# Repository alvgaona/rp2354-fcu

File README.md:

<div align="center">

# rp2354-fcu

**A 40 × 40 mm flight control unit built around the RP2354A.**

</div>

## Overview

rp2354-fcu is a 2-layer flight controller that fits the 30.5 mm mounting pattern. It takes a 2S LiPo or USB, reads an IMU and a GPS, and drives eight servos or ESCs.

- RP2354A microcontroller with 2 MB of flash in the package
- ICM-42688-P IMU on SPI
- GPS connector (JST-GH) for an off-board module such as the NEO-6M
- Eight 3-pin servo/ESC outputs
- 2S LiPo (JST-XH) or USB-C power through a 3.3 V buck converter
- SWD on JST-SH in the Raspberry Pi debug probe pinout

The MCU core (regulator, crystal, decoupling and USB) is copied from Raspberry Pi's RP2350A minimal design, including its layout.

Rev 0.1.0 passes KiCad's ERC and DRC, but it has not been manufactured or tested yet.

The [hardware reference](docs/hardware.md) has the power notes, the GPIO map, the connector pinouts and how to order the board from JLCPCB.

## Build

The design lives in `hw/` and is the source of truth, so edit it in KiCad 10. The build checks it and writes everything you need to order and view the board.

You need KiCad 10 and [pixi](https://pixi.sh). Install the font `hw/fonts/IBMPlexMono-Medium.ttf` first (double-click it), because the text on the back of the board uses it.

```sh
pixi run build
```

The build runs ERC, DRC with schematic parity, and `scripts/check_layout.py`, and stops on any error before it exports anything. That last script checks what DRC cannot. It wants a ground via near every ground pad, the ground pour in one solid piece, no pad fed only by a thin 3.3 V track, and nothing drilled under the IMU.

It then writes these files to `build/`.

- Gerbers, BOM and placement files for JLCPCB (`fc-gerbers.zip`, `fc-bom.csv` and `fc-cpl.csv`)
- The schematic as a PDF (`fc-schematic.pdf`)
- The assembled board in 3D (`fc.glb`)
- The board package with all of the above plus the KiCad files (`fc-rev<rev>.zip`)

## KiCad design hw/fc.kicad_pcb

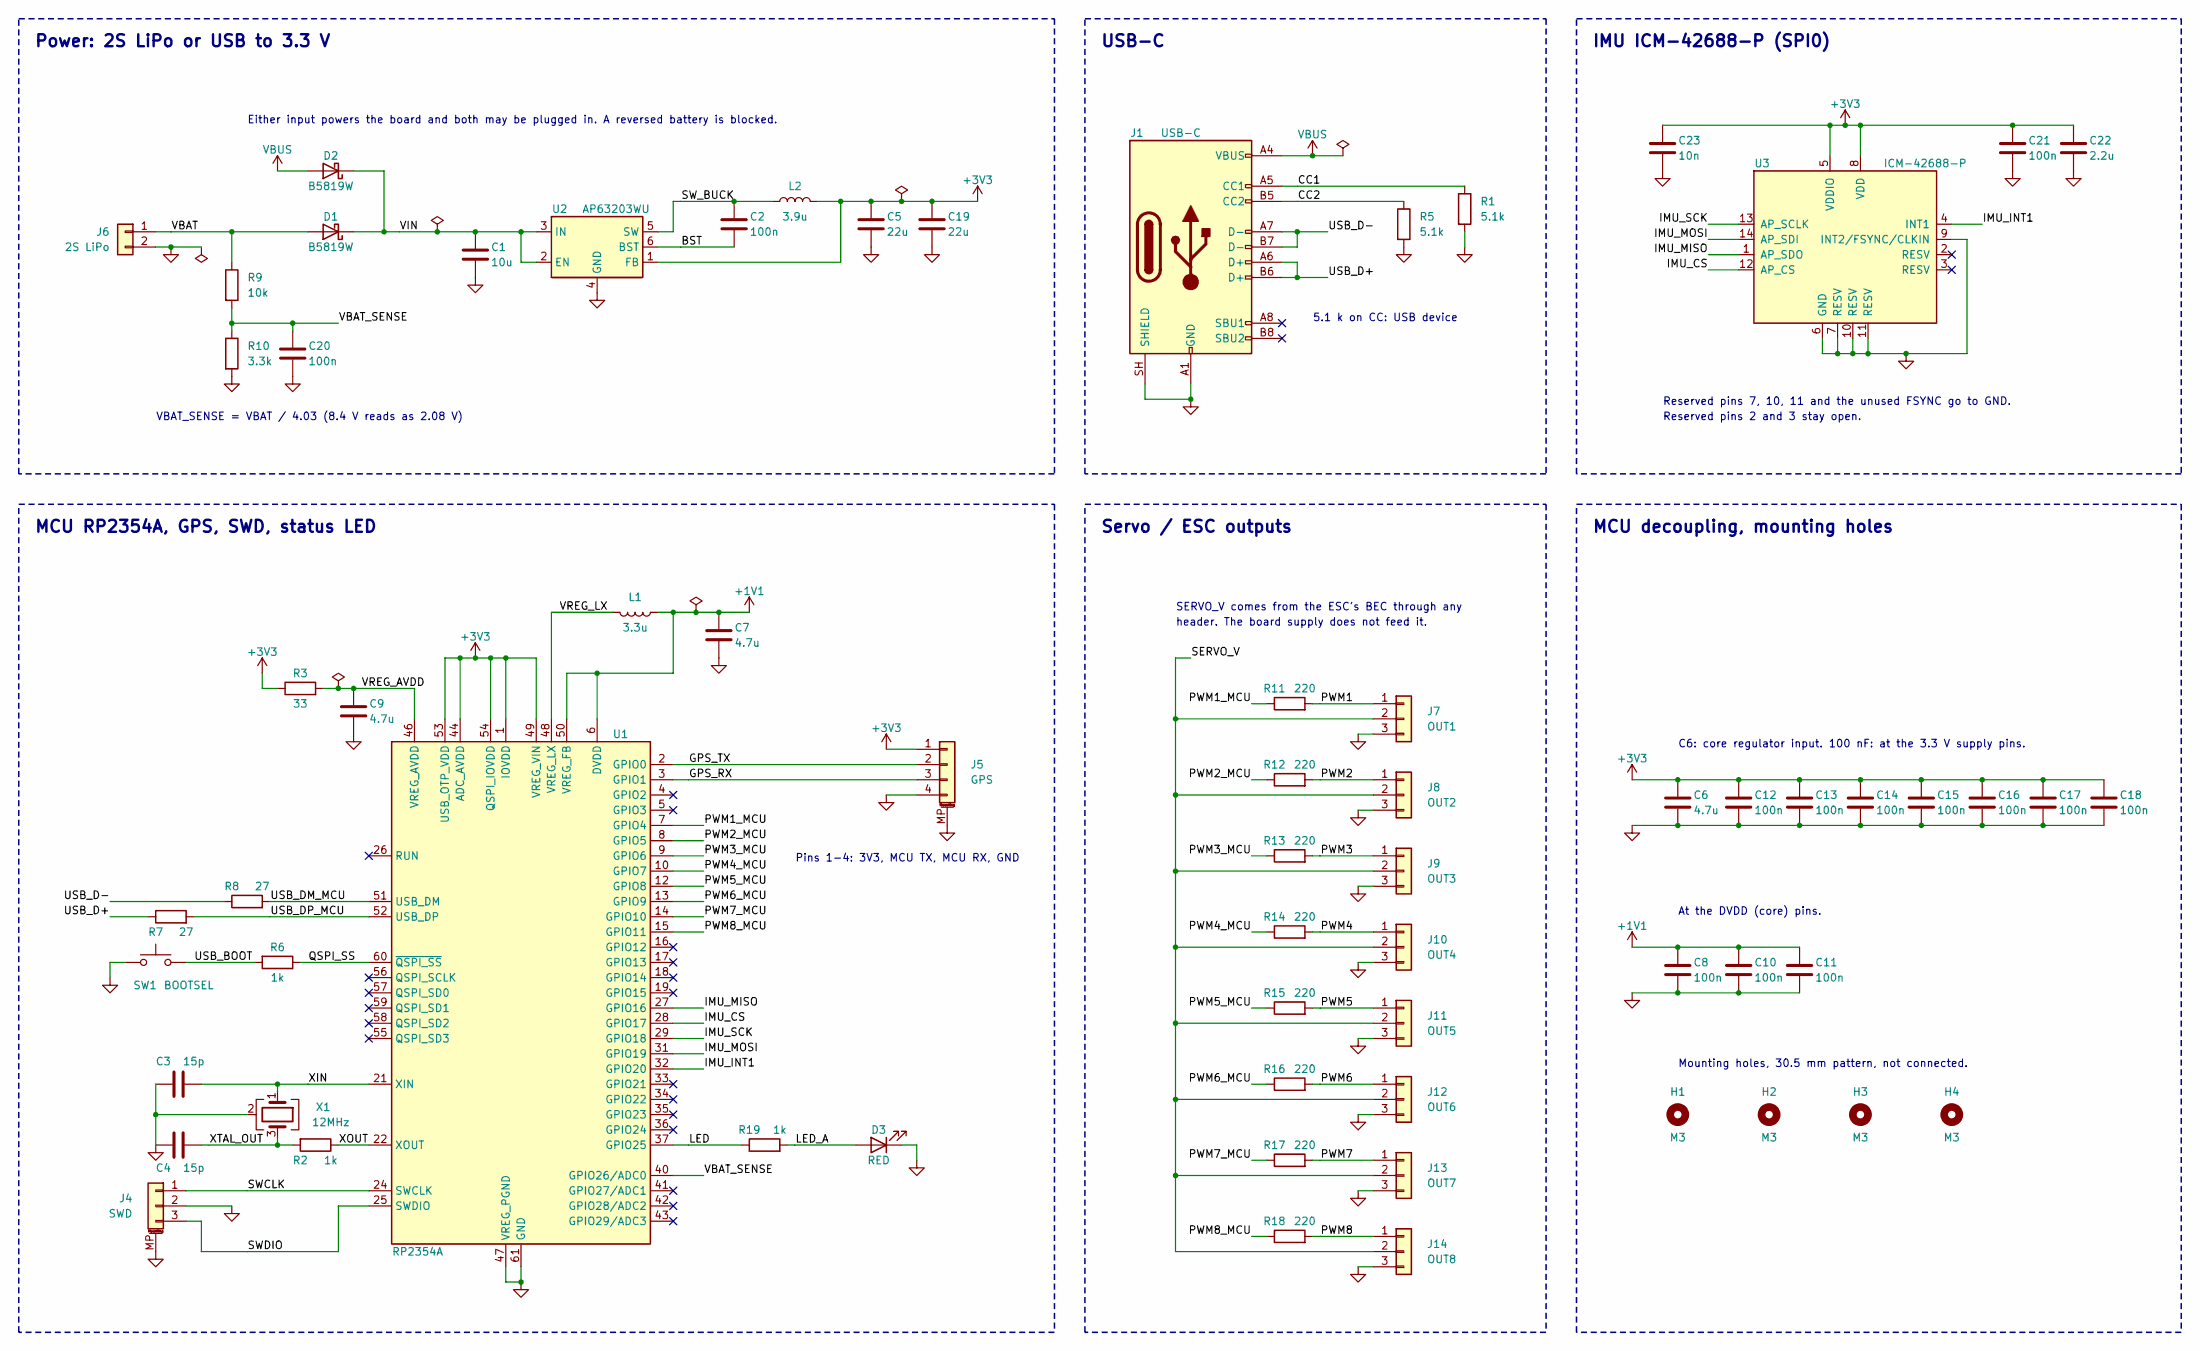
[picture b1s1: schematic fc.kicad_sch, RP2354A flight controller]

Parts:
C1: 10u; C_0805_2012Metric; MPN CL21A106KAYNNNE; LCSC C15850
C2, C20, C21: 100n; C_0402_1005Metric; MPN CL05B104KO5NNNC; LCSC C1525
C3, C4: 15p; generic_capc1005x50; MPN GRM1555C1H150JA01D; LCSC C76950
C5, C19: 22u; C_0805_2012Metric; MPN CL21A226MAQNNNE; LCSC C45783
C6, C7: 4.7u; generic_capc1005x50_wide; MPN GRM155R60J475ME47D; LCSC C82453
C8, C10, C11, C12, C13, C14, C15, C16, C17, C18: 100n; generic_capc1005x50; MPN CL05B104KO5NNNC; LCSC C1525
C9: 4.7u; generic_capc1005x50; MPN GRM155R60J475ME47D; LCSC C82453
C22: 2.2u; C_0402_1005Metric; MPN CL05A225MQ5NSNC; LCSC C12530
C23: 10n; C_0402_1005Metric; MPN CL05B103KB5NNNC; LCSC C15195
D1, D2: B5819W; D_SOD-123; MPN B5819W SL; LCSC C8598
D3: RED; LED_0603_1608Metric; MPN KT-0603R; LCSC C2286
H1, H2, H3, H4: M3; MountingHole_3.2mm_M3
J1: USB-C; USB_C_Receptacle_HRO_TYPE-C-31-M-12; MPN TYPE-C-31-M-12; LCSC C165948
J4: SWD; JST_SH_SM03B-SRSS-TB_1x03-1MP_P1.00mm_Horizontal; MPN SM03B-SRSS-TB(LF)(SN); LCSC C160403
J5: GPS; JST_GH_SM04B-GHS-TB_1x04-1MP_P1.25mm_Horizontal; MPN SM04B-GHS-TB(LF)(SN); LCSC C189895
J6: 2S LiPo; JST_XH_B2B-XH-A_1x02_P2.50mm_Vertical; MPN B2B-XH-A(LF)(SN); LCSC C158012
J7: OUT1; PinHeader_1x03_P2.54mm_Vertical_Tight; MPN 2.54-1*3P; LCSC C49257
J8: OUT2; PinHeader_1x03_P2.54mm_Vertical_Tight; MPN 2.54-1*3P; LCSC C49257
J9: OUT3; PinHeader_1x03_P2.54mm_Vertical_Tight; MPN 2.54-1*3P; LCSC C49257
J10: OUT4; PinHeader_1x03_P2.54mm_Vertical_Tight; MPN 2.54-1*3P; LCSC C49257
J11: OUT5; PinHeader_1x03_P2.54mm_Vertical_Tight; MPN 2.54-1*3P; LCSC C49257
J12: OUT6; PinHeader_1x03_P2.54mm_Vertical_Tight; MPN 2.54-1*3P; LCSC C49257
J13: OUT7; PinHeader_1x03_P2.54mm_Vertical_Tight; MPN 2.54-1*3P; LCSC C49257
J14: OUT8; PinHeader_1x03_P2.54mm_Vertical_Tight; MPN 2.54-1*3P; LCSC C49257
L1: 3.3u; abracon_aota-b201610s3r3-101-t; MPN AOTA-B201610S3R3-101-T; LCSC C42411119
L2: 3.9u; L_Changjiang_FNR3015S; MPN FNR3015S3R9MT; LCSC C167751
R1, R5: 5.1k; R_0402_1005Metric; MPN 0402WGF5101TCE; LCSC C25905
R2: 1k; generic_resc1005x35; MPN 0402WGF1001TCE; LCSC C11702
R3: 33; generic_resc1005x35; MPN 0402WGF330JTCE; LCSC C25105
R6, R19: 1k; R_0402_1005Metric; MPN 0402WGF1001TCE; LCSC C11702
R7, R8: 27; generic_resc1005x35; MPN 0402WGF270JTCE; LCSC C25100
R9: 10k; R_0402_1005Metric; MPN 0402WGF1002TCE; LCSC C25744
R10: 3.3k; R_0402_1005Metric; MPN 0402WGF3301TCE; LCSC C25890
R11, R12, R13, R14, R15, R16, R17, R18: 220; R_0402_1005Metric; MPN 0402WGF2200TCE; LCSC C25091
SW1: BOOTSEL; wurthelek_434133025816; MPN 434133025816; LCSC C5504987
U1: RP2354A; rpi_rp2350a_vias; MPN RP2354A; LCSC C41378174
U2: AP63203WU; TSOT-23-6; MPN AP63203WU-7; LCSC C780769
U3: ICM-42688-P; LGA-14_L3.0-W2.5-P0.50-TL; MPN ICM-42688-P; LCSC C1850418
X1: 12MHz; generic_xtalcc320x250x80-4; MPN ABM8-272-T3; LCSC C20625731

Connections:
+1V1: C7.1, C8.1, C10.1, C11.1, L1.1, U1.6 (DVDD), U1.23 (DVDD), U1.39 (DVDD), U1.50 (VREG_FB)
+3V3: C5.1, C6.1, C12.1, C13.1, C14.1, C15.1, C16.1, C17.1, C18.1, C19.1, C21.1, C22.1, C23.1, J5.1, L2.2, R3.1, U1.1 (IOVDD), U1.11 (IOVDD), U1.20 (IOVDD), U1.30 (IOVDD), U1.38 (IOVDD), U1.44 (ADC_AVDD), U1.45 (IOVDD), U1.49 (VREG_VIN), U1.53 (USB_OTP_VDD), U1.54 (QSPI_IOVDD), U2.1 (FB), U3.5 (VDDIO), U3.8 (VDD)
/BST: C2.1, U2.6 (BST)
/CC1: J1.A5 (CC1), R1.1
/CC2: J1.B5 (CC2), R5.1
/GPS_RX: J5.3, U1.3 (GPIO1)
/GPS_TX: J5.2, U1.2 (GPIO0)
/IMU_CS: U1.28 (GPIO17), U3.12 (AP_CS)
/IMU_INT1: U1.32 (GPIO20), U3.4 (INT1)
/IMU_MISO: U1.27 (GPIO16), U3.1 (AP_SDO)
/IMU_MOSI: U1.31 (GPIO19), U3.14 (AP_SDI)
/IMU_SCK: U1.29 (GPIO18), U3.13 (AP_SCLK)
/LED: R19.1, U1.37 (GPIO25)
/LED_A: D3.2 (A), R19.2
/PWM1: J7.1, R11.2
/PWM1_MCU: R11.1, U1.7 (GPIO4)
/PWM2: J8.1, R12.2
/PWM2_MCU: R12.1, U1.8 (GPIO5)
/PWM3: J9.1, R13.2
/PWM3_MCU: R13.1, U1.9 (GPIO6)
/PWM4: J10.1, R14.2
/PWM4_MCU: R14.1, U1.10 (GPIO7)
/PWM5: J11.1, R15.2
/PWM5_MCU: R15.1, U1.12 (GPIO8)
/PWM6: J12.1, R16.2
/PWM6_MCU: R16.1, U1.13 (GPIO9)
/PWM7: J13.1, R17.2
/PWM7_MCU: R17.1, U1.14 (GPIO10)
/PWM8: J14.1, R18.2
/PWM8_MCU: R18.1, U1.15 (GPIO11)
/QSPI_SS: R6.1, U1.60 (~QSPI_SS)
/SERVO_V: J7.2, J8.2, J9.2, J10.2, J11.2, J12.2, J13.2, J14.2
/SWCLK: J4.1, U1.24 (SWCLK)
/SWDIO: J4.3, U1.25 (SWDIO)
/SW_BUCK: C2.2, L2.1, U2.5 (SW)
/USB_BOOT: R6.2, SW1.3 (B), SW1.4 (B)
/USB_D+: J1.A6 (D+), J1.B6 (D+), R7.1
/USB_D-: J1.A7 (D-), J1.B7 (D-), R8.1
/USB_DM_MCU: R8.2, U1.51 (USB_DM)
/USB_DP_MCU: R7.2, U1.52 (USB_DP)
/VBAT: D1.2 (A), J6.1, R9.1
/VBAT_SENSE: C20.1, R9.2, R10.1, U1.40 (GPIO26/ADC0)
/VIN: C1.1, D1.1 (K), D2.1 (K), U2.2 (EN), U2.3 (IN)
/VREG_AVDD: C9.1, R3.2, U1.46 (VREG_AVDD)
/VREG_LX: L1.2, U1.48 (VREG_LX)
/XIN: C3.1, U1.21 (XIN), X1.1
/XOUT: R2.1, U1.22 (XOUT)
/XTAL_OUT: C4.1, R2.2, X1.3
GND: C1.2, C3.2, C4.2, C5.2, C6.2, C7.2, C8.2, C9.2, C10.2, C11.2, C12.2, C13.2, C14.2, C15.2, C16.2, C17.2, C18.2, C19.2, C20.2, C21.2, C22.2, C23.2, D3.1 (K), J1.A1 (GND), J1.A12 (GND), J1.B1 (GND), J1.B12 (GND), J1.SH (SHIELD), J4.2, J4.MP (MountPin), J5.4, J5.MP (MountPin), J6.2, J7.3, J8.3, J9.3, J10.3, J11.3, J12.3, J13.3, J14.3, R1.2, R5.2, R10.2, SW1.1 (A), SW1.2 (A), U1.47 (VREG_PGND), U1.61 (GND), U2.4 (GND), U3.6 (GND), U3.7 (RESV), U3.9 (INT2/FSYNC/CLKIN), U3.10 (RESV), U3.11 (RESV), X1.2 (G), X1.4 (G)
VBUS: D2.2 (A), J1.A4 (VBUS), J1.A9 (VBUS), J1.B4 (VBUS), J1.B9 (VBUS)

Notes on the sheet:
Either input powers the board and both may be plugged in. A reversed battery is blocked.
VBAT_SENSE = VBAT / 4.03 (8.4 V reads as 2.08 V)
Pins 1-4: 3V3, MCU TX, MCU RX, GND
5.1 k on CC: USB device
SERVO_V comes from the ESC's BEC through any
header. The board supply does not feed it.
Reserved pins 7, 10, 11 and the unused FSYNC go to GND.
Reserved pins 2 and 3 stay open.
C6: core regulator input. 100 nF: at the 3.3 V supply pins.
At the DVDD (core) pins.
Mounting holes, 30.5 mm pattern, not connected.
Power: 2S LiPo or USB to 3.3 V
MCU RP2354A, GPS, SWD, status LED
USB-C
Servo / ESC outputs
IMU ICM-42688-P (SPI0)
MCU decoupling, mounting holes

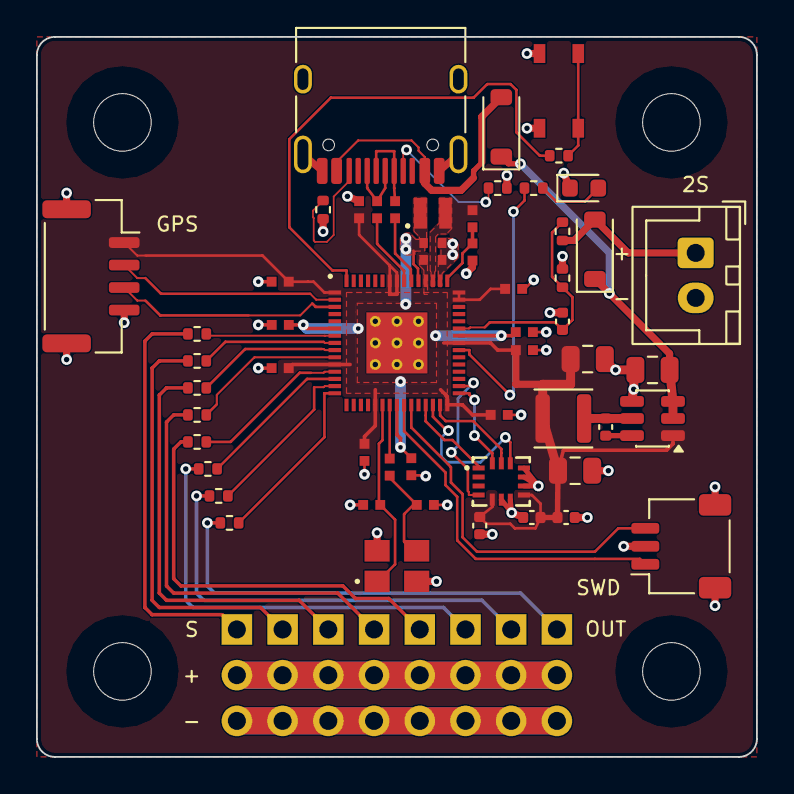
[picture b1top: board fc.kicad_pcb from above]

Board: 2 copper layers, 40.0 x 40.0 mm, 67 parts (0 on the bottom side), 50 nets.

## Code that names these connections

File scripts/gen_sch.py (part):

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    s.w(r9["2"], r10["1"])
    s.w((27.94, 45.72), (38.1, 45.72), c20["1"])
    s.w((38.1, 45.72), (45.72, 45.72))
    s.label("VBAT_SENSE", (45.72, 45.72))
    s.power("GND", r10["2"])
    s.power("GND", c20["2"])
    s.text("VBAT_SENSE = VBAT / 4.03 (8.4 V reads as 2.08 V)", 15.24, 62.23)
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    l2 = s.place("L2", 121.92, 25.4, a=90)
    c2 = s.place("C2", 111.76, 29.21, a=180)
    s.w(u2["5"], (101.6, 30.48), (101.6, 25.4), l2["1"])
    s.label("SW_BUCK", (102.87, 25.4))
    s.w(u2["6"], c2["1"])
    s.label("BST", (102.87, 33.02))
    s.w(l2["2"], (152.4, 25.4))
    s.w(u2["1"], (129.54, 35.56), (129.54, 25.4))
    for ref, x in (("C5", 134.62), ("C19", 144.78)):
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
def imu_block(s):
    u3 = s.place("U3", 60.96, 45.72, val_at=(67.31, 31.75, "left"))
    for pin, name, a in (("13", "IMU_SCK", 180), ("14", "IMU_MOSI", 180), ("1", "IMU_MISO", 180), ("12", "IMU_CS", 180),
                         ("4", "IMU_INT1", 0)):
        end = (u3[pin][0] + (5.08 if a == 0 else -5.08), u3[pin][1])
        s.w(u3[pin], end)
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    r3 = s.place("R3", 64.77, 50.8, a=90)
    c9 = s.place("C9", 73.66, 54.61)
    s.w(u1["46"], (83.82, 50.8), r3["2"])
    s.label("VREG_AVDD", (74.93, 50.8))
    s.power("FLAG", (71.12, 50.8))
    s.w(r3["1"], (58.42, 50.8), (58.42, 48.26))
    s.power("+3V3", (58.42, 48.26))
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    l1 = s.place("L1", 120.65, 38.1, a=270)
    c7 = s.place("C7", 134.62, 41.91)
    s.w(u1["48"], (106.68, 38.1), l1["2"])
    s.label("VREG_LX", (107.95, 38.1))
    s.w(l1["1"], (139.7, 38.1))
    s.w((127, 38.1), (127, 48.26), (109.22, 48.26), u1["50"])
    s.w(u1["6"], (114.3, 48.26))
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    r6 = s.place("R6", 60.96, 96.52, a=270)
    sw = s.place("SW1", 40.64, 96.52, ref_at=(36.83, 100.33, "left"), val_at=(41.91, 100.33, "left"))
    s.w(u1["60"], r6["1"])
    s.label("QSPI_SS", (66.04, 96.52))
    s.w(r6["2"], sw["3"])
    s.label("USB_BOOT", (46.99, 96.52))
    s.w(sw["1"], (33.02, 96.52), (33.02, 99.06))
    s.power("GND", (33.02, 99.06))

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    r2_ = s.place("R2", 67.31, 127, a=270, ref_at=(64.77, 129.54, None), val_at=(69.85, 129.54, None))
    s.w(u1["21"], c3["1"])
    s.w((60.96, 116.84), x1["1"])
    s.label("XIN", (66.04, 116.84))
    s.w(u1["22"], r2_["1"])
    s.label("XOUT", (71.12, 127))
    s.w(r2_["2"], c4["1"])
    s.w((60.96, 127), x1["3"])
    s.label("XTAL_OUT", (49.53, 127))
    s.w(c3["2"], c4["2"])
    s.w(x1["2"], (40.64, 121.92))
    s.power("GND", c4["2"])
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    # right: GPS connector straight across from UART0, signals that leave the block, status LED
    j5 = s.place("J5", 172.72, 63.5, ref_at=(176.53, 63.5, "left"), val_at=(176.53, 66.04, "left"))
    s.w(u1["2"], j5["2"])
    s.label("GPS_TX", (129.54, 63.5))
    s.w(u1["3"], j5["3"])
    s.label("GPS_RX", (129.54, 66.04))
    s.w(j5["1"], (162.56, 60.96))
    s.power("+3V3", (162.56, 60.96))
    s.w(j5["4"], (162.56, 68.58))
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    s.w(u1["37"], r19["1"])
    s.label("LED", (129.54, 127))
    s.w(r19["2"], d3["2"])
    s.label("LED_A", (147.32, 127))
    s.w(d3["1"], (167.64, 127), (167.64, 129.54))
    s.power("GND", (167.64, 129.54))

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        s.power("GND", (35.56, j["3"][1]))
        last = j["2"][1]
    s.w((7.62, 12.7), (5.08, 12.7), (5.08, last))
    s.label("SERVO_V", (7.62, 12.7))
    s.text("SERVO_V comes from the ESC's BEC through any", 5.08, 5.08)
    s.text("header. The board supply does not feed it.", 5.08, 7.62)

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
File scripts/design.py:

"""Single source of truth for the rev 0.1.0 flight-controller board.

Every part: ref -> (symbol, value, footprint, MPN, manufacturer, LCSC, {pin: net}).
Pins not listed get a no-connect flag. Refs of the RP2354A support circuit match
Raspberry Pi's RP2350A minimal design so build_pcb.py can transplant its layout.
"""

REV = "0.1.0"
TITLE = "RP2354A flight controller"

R0402 = "Resistor_SMD:R_0402_1005Metric"
C0402 = "Capacitor_SMD:C_0402_1005Metric"
C0805 = "Capacitor_SMD:C_0805_2012Metric"
# Footprints copied from the Raspberry Pi minimal design (layout transplanted as-is).
RC = "rpi:generic_capc1005x50"
RCW = "rpi:generic_capc1005x50_wide"
RR = "rpi:generic_resc1005x35"

PARTS = {}


def part(ref, sym, value, fp, mpn, mfr, lcsc, pins):
    PARTS[ref] = dict(sym=sym, value=value, fp=fp, mpn=mpn, mfr=mfr, lcsc=lcsc, pins=pins)


def R(ref, value, a, b, mpn, lcsc, fp=R0402):
    part(ref, "Device:R", value, fp, mpn, "UNI-ROYAL", lcsc, {"1": a, "2": b})


def C(ref, value, a, b, mpn, mfr, lcsc, fp=C0402):
    part(ref, "Device:C", value, fp, mpn, mfr, lcsc, {"1": a, "2": b})


# ---------------- MCU: RP2354A (2 MB flash in package) ----------------
GPIO = {
    2: "GPS_TX", 3: "GPS_RX",  # GPIO0/1 = UART0
    # GPIO4-11 = PWM slices 2-5. GPIO2/3 (pins 4/5) are left free: C8's vias block their escape.
    7: "PWM1_MCU", 8: "PWM2_MCU", 9: "PWM3_MCU", 10: "PWM4_MCU",
    12: "PWM5_MCU", 13: "PWM6_MCU", 14: "PWM7_MCU", 15: "PWM8_MCU",
    27: "IMU_MISO", 28: "IMU_CS", 29: "IMU_SCK", 31: "IMU_MOSI",  # GPIO16-19 = SPI0
    32: "IMU_INT1",  # GPIO20
    37: "LED",  # GPIO25
    40: "VBAT_SENSE",  # GPIO26/ADC0
}
u1 = {str(p): "+3V3" for p in (1, 11, 20, 30, 38, 45, 44, 49, 53, 54)}
u1.update({str(p): "+1V1" for p in (6, 23, 39, 50)})
u1.update({str(p): n for p, n in GPIO.items()})
# RUN has an internal pull-up; the optional reset button is omitted (power-cycle instead).
u1.update({"21": "XIN", "22": "XOUT", "24": "SWCLK", "25": "SWDIO",
           "46": "VREG_AVDD", "47": "GND", "48": "VREG_LX", "51": "USB_DM_MCU", "52": "USB_DP_MCU",
           "60": "QSPI_SS", "61": "GND"})
part("U1", "MCU_RaspberryPi:RP2354A", "RP2354A", "rpi:rpi_rp2350a_vias", "RP2354A", "Raspberry Pi", "C41378174", u1)

# Core regulator (exact parts required by the RP2350 hardware design guide)
part("L1", "Device:L", "3.3u", "rpi:abracon_aota-b201610s3r3-101-t", "AOTA-B201610S3R3-101-T", "Abracon", "C42411119",
     {"1": "+1V1", "2": "VREG_LX"})
for ref, a in (("C6", "+3V3"), ("C7", "+1V1"), ("C9", "VREG_AVDD")):
    C(ref, "4.7u", a, "GND", "GRM155R60J475ME47D", "Murata", "C82453", fp=RCW if ref != "C9" else RC)
R("R3", "33", "+3V3", "VREG_AVDD", "0402WGF330JTCE", "C25105", fp=RR)
for ref in ("C8", "C10", "C11"):
    C(ref, "100n", "+1V1", "GND", "CL05B104KO5NNNC", "Samsung", "C1525", fp=RC)
for ref in ("C12", "C13", "C14", "C15", "C16", "C17", "C18"):
    C(ref, "100n", "+3V3", "GND", "CL05B104KO5NNNC", "Samsung", "C1525", fp=RC)

# Crystal (ABM8-272-T3 + 15p + 1k, as specified by Raspberry Pi)
part("X1", "Device:Crystal_GND24", "12MHz", "rpi:generic_xtalcc320x250x80-4", "ABM8-272-T3", "Abracon", "C20625731",
     {"1": "XIN", "2": "GND", "3": "XTAL_OUT", "4": "GND"})
C("C3", "15p", "XIN", "GND", "GRM1555C1H150JA01D", "Murata", "C76950", fp=RC)
C("C4", "15p", "XTAL_OUT", "GND", "GRM1555C1H150JA01D", "Murata", "C76950", fp=RC)
R("R2", "1k", "XOUT", "XTAL_OUT", "0402WGF1001TCE", "C11702", fp=RR)

# USB-C (device, 5.1k Rd on CC) + 27R series termination close to the chip
part("J1", "Connector:USB_C_Receptacle_USB2.0_16P", "USB-C", "fc:USB_C_Receptacle_HRO_TYPE-C-31-M-12",
     "TYPE-C-31-M-12", "HRO", "C165948",
     {"A1": "GND", "B1": "GND", "A12": "GND", "B12": "GND", "SH": "GND",
      "A4": "VBUS", "B4": "VBUS", "A9": "VBUS", "B9": "VBUS",
      "A5": "CC1", "B5": "CC2", "A6": "USB_D+", "B6": "USB_D+", "A7": "USB_D-", "B7": "USB_D-"})
R("R1", "5.1k", "CC1", "GND", "0402WGF5101TCE", "C25905")
R("R5", "5.1k", "CC2", "GND", "0402WGF5101TCE", "C25905")
R("R7", "27", "USB_D+", "USB_DP_MCU", "0402WGF270JTCE", "C25100", fp=RR)
R("R8", "27", "USB_D-", "USB_DM_MCU", "0402WGF270JTCE", "C25100", fp=RR)

# BOOTSEL button, SWD debug (Raspberry Pi debug-probe pinout)
SW = "rpi:wurthelek_434133025816"
part("SW1", "Switch:SW_MEC_5G", "BOOTSEL", SW, "434133025816", "Wurth Elektronik", "C5504987",
     {"1": "GND", "2": "GND", "3": "USB_BOOT", "4": "USB_BOOT"})
R("R6", "1k", "QSPI_SS", "USB_BOOT", "0402WGF1001TCE", "C11702")
part("J4", "Connector_Generic_MountingPin:Conn_01x03_MountingPin", "SWD",
     "Connector_JST:JST_SH_SM03B-SRSS-TB_1x03-1MP_P1.00mm_Horizontal", "SM03B-SRSS-TB(LF)(SN)", "JST", "C160403",
     {"1": "SWCLK", "2": "GND", "3": "SWDIO", "MP": "GND"})
part("D3", "Device:LED", "RED", "LED_SMD:LED_0603_1608Metric", "KT-0603R", "Hubei KENTO", "C2286",
     {"1": "GND", "2": "LED_A"})
R("R19", "1k", "LED", "LED_A", "0402WGF1001TCE", "C11702")

# ---------------- Power: 2S LiPo / USB -> diode-OR -> AP63203 buck -> 3.3 V ----------------
part("J6", "Connector_Generic:Conn_01x02", "2S LiPo", "Connector_JST:JST_XH_B2B-XH-A_1x02_P2.50mm_Vertical",
     "B2B-XH-A(LF)(SN)", "JST", "C158012", {"1": "VBAT", "2": "GND"})
part("D1", "Device:D_Schottky", "B5819W", "Diode_SMD:D_SOD-123", "B5819W SL", "CJ", "C8598",
     {"1": "VIN", "2": "VBAT"})  # reverse-polarity protection + OR with USB
part("D2", "Device:D_Schottky", "B5819W", "Diode_SMD:D_SOD-123", "B5819W SL", "CJ", "C8598",
     {"1": "VIN", "2": "VBUS"})
part("U2", "Regulator_Switching:AP63203WU", "AP63203WU", "Package_TO_SOT_SMD:TSOT-23-6", "AP63203WU-7",
     "Diodes Inc", "C780769", {"1": "+3V3", "2": "VIN", "3": "VIN", "4": "GND", "5": "SW_BUCK", "6": "BST"})
C("C1", "10u", "VIN", "GND", "CL21A106KAYNNNE", "Samsung", "C15850", fp=C0805)
C("C2", "100n", "BST", "SW_BUCK", "CL05B104KO5NNNC", "Samsung", "C1525")
part("L2", "Device:L", "3.9u", "Inductor_SMD:L_Changjiang_FNR3015S", "FNR3015S3R9MT", "Changjiang", "C167751",
     {"1": "SW_BUCK", "2": "+3V3"})
C("C5", "22u", "+3V3", "GND", "CL21A226MAQNNNE", "Samsung", "C45783", fp=C0805)
C("C19", "22u", "+3V3", "GND", "CL21A226MAQNNNE", "Samsung", "C45783", fp=C0805)
# Battery voltage sense: 10k/3.3k -> 8.4 V reads 2.08 V on ADC0
R("R9", "10k", "VBAT", "VBAT_SENSE", "0402WGF1002TCE", "C25744")
R("R10", "3.3k", "VBAT_SENSE", "GND", "0402WGF3301TCE", "C25890")
C("C20", "100n", "VBAT_SENSE", "GND", "CL05B104KO5NNNC", "Samsung", "C1525")

# ---------------- IMU: ICM-42688-P on SPI0 ----------------
part("U3", "fc:ICM-42688-P", "ICM-42688-P", "easyeda:LGA-14_L3.0-W2.5-P0.50-TL", "ICM-42688-P",
     "TDK InvenSense", "C1850418",
     # RESV pins 2, 3, 10, 11 are "no connect or GND" in the datasheet. 2 and 3 are left open so the INT1
     # track can pass them; 10 and 11 are grounded together with pin 9 (FSYNC, unused) to share its via.
     # Pin 7 (RESV) must be GND.
     {"1": "IMU_MISO", "4": "IMU_INT1", "5": "+3V3", "6": "GND", "7": "GND",
      "8": "+3V3", "9": "GND", "10": "GND", "11": "GND", "12": "IMU_CS", "13": "IMU_SCK", "14": "IMU_MOSI"})
C("C21", "100n", "+3V3", "GND", "CL05B104KO5NNNC", "Samsung", "C1525")  # VDD
C("C22", "2.2u", "+3V3", "GND", "CL05A225MQ5NSNC", "Samsung", "C12530")  # VDD
C("C23", "10n", "+3V3", "GND", "CL05B103KB5NNNC", "Samsung", "C15195")  # VDDIO

# ---------------- External connections ----------------
part("J5", "Connector_Generic_MountingPin:Conn_01x04_MountingPin", "GPS",
     "Connector_JST:JST_GH_SM04B-GHS-TB_1x04-1MP_P1.25mm_Horizontal", "SM04B-GHS-TB(LF)(SN)", "JST", "C189895",
     {"1": "+3V3", "2": "GPS_TX", "3": "GPS_RX", "4": "GND", "MP": "GND"})
for i in range(1, 9):
    R(f"R{10 + i}", "220", f"PWM{i}_MCU", f"PWM{i}", "0402WGF2200TCE", "C25091")
    # signal / servo rail (fed by ESC BEC, isolated from 3V3) / GND
    part(f"J{6 + i}", "Connector_Generic:Conn_01x03", f"OUT{i}", "fc:PinHeader_1x03_P2.54mm_Vertical_Tight",
         "2.54-1*3P", "BOOMELE", "C49257", {"1": f"PWM{i}", "2": "SERVO_V", "3": "GND"})
for i in range(1, 5):
    part(f"H{i}", "Mechanical:MountingHole", "M3", "MountingHole:MountingHole_3.2mm_M3", "", "", "", {})

def nets():
    out = {}
    for ref, p in PARTS.items():
        for pin, net in p["pins"].items():
            out.setdefault(net, []).append((ref, pin))
    return out


if __name__ == "__main__":
    for n, conns in sorted(nets().items()):
        if len(conns) < 2:
            print("SINGLE-PIN NET", n, conns)
    print(len(PARTS), "parts", len(nets()), "nets")
